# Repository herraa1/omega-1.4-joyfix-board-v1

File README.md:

# Omega Mainboard Revision 1.4 JoyFix Board

This is an interposer board that fixes the existing bug in the joystick circuit of the Omega Mainboard revision 1.4 of the [Omega Home Computer](https://github.com/skiselev/omega) by Sergey Kiselev.

> [!NOTE]
> This fix is not needed if you already have a [Omega Mainboard revision 1.5](https://github.com/skiselev/omega/blob/master/Mainboard.md#changes), which includes the joystick circuit fix.

# The standard MSX joystick circuit

The MSX specification requires that compatible computers provide one or two joystick ports. Nevertheless, most MSX computers have two joystick ports.

The MSX joystick ports are controlled by an AY-3-8910 (or compatible) chip, called the PSG (Programmable Sound Generator). This chip has two general I/O ports IOA and IOB to interface with a micro-processor. In the case of the MSX, IOB is used as OUTPUT and mapped to register #15 of PSG, and IOA is used as INPUT and mapped to register #14 of PSG.

||
|:--|
|MSX Joystick Circuit Diagram|

In the diagram:
- J3 represents joystick port 1
- J4 represents joystick port 2

Each one of the joystick ports has the following pinout:
- 4x INPUT signals
  - pin 1:UP
  - pin 2:DOWN
  - pin 3:LEFT
  - pin 4:RIGHT
- 2x INPUT/OUTPUT signals
  - pin 6:TRIGGER A
  - pin 7:TRIGGER B
- 1x OUTPUT signal
  - pin 8:OUTPUT
- 2x POWER lines
  - pin 5: +5V
  - pin 9: GND

INPUT signals and the input side of INPUT/OUTPUT signals are pulled up by default (making them logical "1" while floating).

The output side of INPUT/OUTPUT signals are buffered with open-collector buffers (74LS07), which leave the outputs floating on logical input "1" and pulled down on logical input "0".

The OUTPUT signal is a push-pull signal, so the output does not float and it is always set to logical "0" or "1".

## IOB I/O port (PSG register #15, OUTPUT) ##

IOB bit 0 controls the output logical level of TRIGGER A (pin 6) of joystick port 1.

IOB bit 1 controls the output logical level of TRIGGER B (pin 7) of joystick port 1.

IOB bit 2 controls the output logical level of TRIGGER A (pin 6) of joystick port 2.

IOB bit 3 controls the output logical level of TRIGGER B (pin 7) of joystick port 2.

IOB bit 4 controls the output logical level of OUTPUT (pin 8) of joystick port 1.

IOB bit 5 controls the output logical level of OUTPUT (pin 8) of joystick port 2.

IOB bit 6 controls which joystick is read ("0" for joystick port 1 and "1" for joystick port 2) as it is connected directly to the Select signal (pin 1) of two 74LS157 quad 2-input multiplexers used to select between the signals of each joystick port.

## IOA I/O port (PSG register #14, INPUT) ##

IOA bits read the status of the direction arrows and triggers of the joysticks. A "1" indicates an inactive arrow/trigger, and a "0" indicates a pressed arrow/trigger.

Before reading an arrow/trigger of a specific joystick, IOB bit 6 must be set accordingly to select the proper joystick port ("0" for port 1, "1" for port 2).

In addition, due to the electrical characteristics of the MSX joystick circuit, reading the trigger buttons input side from IOA require making sure that the output side of IOB is set to "1" before (to avoid pulling down/clobbering the signal).
- In order to read TRIGGER A (bit 4 of IOA) of joystick port 1, one needs to write "1" to bit 0 of IOB.
- In order to read TRIGGER B (bit 5 of IOA) of joystick port 1, one needs to write "1" to bit 1 of IOB.
- In order to read TRIGGER A (bit 4 of IOA) of joystick port 2, one needs to write "1" to bit 2 of IOB.
- In order to read TRIGGER B (bit 5 of IOA) of joystick port 2, one needs to write "1" to bit 3 of IOB.

IOA bit 0 reads the status of the UP arrow.

IOA bit 1 reads the status of the DOWN arrow.

IOA bit 2 reads the status of the LEFT arrow.

IOA bit 3 reads the status of the RIGHT arrow.

IOA bit 4 reads the status of the TRIGGER A button.

IOA bit 5 reads the status of the TRIGGER B button.

# The Problem

As described in the [MRC](https://www.msx.org) hardware forum, @PaxNL discovered an [issue](https://www.msx.org/forum/msx-talk/hardware/msxmakers-support?page=17) with [Super Sokoban](https://www.msxdev.org/2025/01/28/msxdev24-28-super-sokoban/) when trying to play the game with a joystick on the [Omega Home Computer](https://github.com/skiselev/omega).

The game uses the [MSXgl](https://aoineko.org/msxgl/index.php?title=Modules/input) library device detection feature which uses a [MSX-HID](https://www.msx.org/wiki/MSX-HID)-like device fingerprinting to support joysticks and other input devices.

The detection uses OUTPUT (pin 8) of the [joystick port](https://www.msx.org/wiki/General_Purpose_port) to generate a 3-cycle LOW-HIGH-LOW signal. At each of those cycles the low order bits 0-5 of PSG register #14 are read and a fingerprint is calculated based on the results of the 3-cycle reads. The generated fingerprint (hopefully) identifies the connected device type, and from there the proper I/O protocol is used to read/write data to the connected device (which may include using the trigger ports as outputs).

While troubleshooting the issue, @PaxNL and @Arjan determined by looking at the joystick port readouts that there was a problem with the joystick I/O: TRIGGER B on joystick port 1 and TRIGGER A on joystick port 2 were always detected as pressed when the game was run on the Omega Home Computer.

After a deeper analysis with the help of @aoineko, the author of MSXgl, it was determined that there was an implementation bug in the Omega Home Computer joystick circuit diagram which caused exactly that behavior as a result of the software interaction with the buggy hardware.

> [!NOTE]
> The joystick circuit bug does not affect normal operation of joysticks if the software never writes a "0" to the trigger outputs, which is the case for the vast majority of games that use just MSX joysticks and no other devices connected to the joystick ports.
> That's probably why the bug remained undetected for such a long time.

# The Omega mainboard 1.4 joystick circuit

As can be seen on the depicted diagram, the Omega Home Computer PSG circuit tries to mimic the standard MSX joystick circuit, but has a subtle implementation flaw.

Some useful signal mappings to understand the circuit:
- JB0 signal maps to IOB0 signal
- JB1 signal maps to IOB1 signal
- JB2 signal maps to IOB2 signal
- JB3 signal maps to IOB3 signal

If we look closely at the connection of the trigger output signals to the open-collector buffer inputs and the connection of the open-collector buffer outputs to the joystick port signals we can see that:
- :white_check_mark: the output of the open-collector buffer corresponding to signal JB0 (IOB0) is connected to joystick port 1 trigger A (TRG1_A)
- :x: the output of the open-collector buffer corresponding to signal JB1 (IOB1) is incorrectly connected to joystick port 2 trigger A (TRG1_B)
- :x: the output of the open-collector buffer corresponding to signal JB2 (IOB2) is incorrectly connected to joystick port 1 trigger B (TRG2_A)
- :white_check_mark: the output of the open-collector buffer corresponding to signal JB3 (IOB3) is connected to joystick port 2 trigger B (TRG2_B)

Exactly the two signals that were incorrectly read (joystick port 2 trigger A and joystick port 1 trigger B) are the signals that are incorrectly wired.

The incorrect wiring is probably caused by the confusing naming convention used for the trigger signal labels which is prone to errors (TRGx_y means trigger x of joystick y, with y=A|B and x=1|2).

# The fix

The circuit can be easily fixed by re-routing the affected signals to make them available at the right place.

In the Omega Mainboard 1.4 joystick circuit we have the following connections related to the triggers, taking into account the functional pinout of the [74LS07](https://www.ti.com/lit/ds/symlink/sn74ls07.pdf):
- input `Pin 11` of U42 (connected to JB2/IOB2) outputs to `Pin 10` of U42 (incorrectly connected to joystick port 1 trigger B, aka TRG2_A)
- input `Pin 13` of U42 (connected to JB1/IOB1) outputs to `Pin 12` of U42 (incorrectly connected to joystick port 2 trigger A, aka TRG1_B)

A clean and easy approach to fix the circuit is to use an interposer board at U42 (74LS07 open-collector buffer) that performs the needed re-mapping of signals.

The idea of the interposer board was brought up by Ludo and shared on [issue #56](https://github.com/skiselev/omega/issues/56) of the [Omega github page](https://github.com/skiselev/omega) where you can see a photo of his CNC fabricated interposer board.

So to re-route the signals to match the MSX standard joystick circuit we can map the U42-original signals to a new set of U42-interposed signals (where the 74LS07 will be actually connected), like this:
- Connect `Pin 10 of U42-interposed` (buffered output of Pin 11 of U42-interposed which connects to JB2/IOB2) to `Pin 12 of U42-original` (connected to joystick port 2 trigger A, aka TRG1_B), so that Pin 11 of U42-original (JB2/IOB2) outputs to Pin 12 of U42-original (joystick port 2 trigger A) ( `yellow` path on the diagram)
- Connect `Pin 12 of U42-interposed` (buffered output of Pin 13 of U42-interposed which connects to JB1/IOB1) to `Pin 10 of U42-original` (connected to joystick port 1 trigger B, aka TRG2_A), so that Pin 13 of U42-original (JB1/IOB1) outputs to Pin 10 of U42-original (joystick port 1 trigger B) ( `green` path on the diagram)
- Connect all other Pins of U42-interposed to the same Pins of U42-original (i.e Pin 1 to Pin 1, Pin 2 to Pin 2, etc.) ( solid `pink` paths on the diagram)

Summarizing, after the re-routing we have fixed the issue:
- `Pin 11 of U42-original` (connected to JB2/IOB2) outputs to `Pin 12 of U42-original` (connected to joystick port 2 trigger A)
- `Pin 13 of U42-original` (connected to JB1/IOB1) outputs to `Pin 10 of U42-original` (connected to joystick port 1 trigger B)

And the complete trigger connection diagram matches now the original MSX joystick circuit diagram:
- :white_check_mark: the output at the open-collector buffer corresponding to signal JB0 (IOB0) is connected to joystick port 1 trigger A (TRG1_A)
- :white_check_mark: the output at the open-collector buffer corresponding to signal JB1 (IOB1) is connected to joystick port 1 trigger B (TRG2_A)
- :white_check_mark: the output at the open-collector buffer corresponding to signal JB2 (IOB2) is connected to joystick port 2 trigger A (TRG1_B)
- :white_check_mark: the output at the open-collector buffer corresponding to signal JB3 (IOB3) is connected to joystick port 2 trigger B (TRG2_B)

# Hardware

## [Omega-1.4-U42-joyfix-v1-Build1](hardware/kicad/omega-1.4-joyfix-board-v1-Build1/)

:white_check_mark: This board has been successfully built and tested.

[Bill Of Materials (BoM)](https://htmlpreview.github.io/?https://raw.githubusercontent.com/herraa1/omega-1.4-joyfix-board-v1/main/hardware/kicad/omega-1.4-joyfix-board-v1-Build1/bom/ibom.html)

[Schematic and PCB](https://kicanvas.org/?github=https%3A%2F%2Fgithub.com%2Fherraa1%2Fomega-1.4-joyfix-board-v1%2Ftree%2Fmain%2Fhardware%2Fkicad%2Fomega-1.4-joyfix-board-v1-Build1)

## PCB Manufacturing tips

As the joyfix board is super small, some PCB manufacturers may make extra charges when building standalone prototypes or panelizing the boards using v-cuts.

One way to avoid the extra costs is panelizing the joyfix board using "mouse bites".

# Build instructions

## Required materials

* 2x 2.54mm pitch male-male header L10 7P
* 1x DIP14 circular IC socket

## Step by step instructions

1. Determine the large pad side of the 7P headers.

2. Temporarily insert the two 7P headers into the DIP14 circular IC socket to perfectly align the headers before soldering them to the joyfix board PCB.

You need to insert the headers so that the large pad side stays on the top, and the small pads side is inserted into the socket.

3. Insert the PCB into the two 7P headers using the small circular pads, making sure the PCB top mark remains at the top.

4. Solder the headers to the PCB from the top side and then remove the DIP14 IC socket (it was used temporarily just for alignment purposes).

5. Trim the headers on the top side to avoid interfering with the DIP14 IC socket when installed permanently.

6. Insert the DIP14 IC socket into the large pads of the PCB from the top side in preparation for soldering.

7. Solder the DIP14 IC socket to the joyfix board PCB from the bottom side, making sure you don't accidentally touch the header plastics while soldering.

8. Clean the board with 99.9% Isopropyl Alcohol (IPA) and proceed to installation.

# Installation instructions

## Step by step instructions

1. Locate the U42 74LS07 IC chip on the Omega Home Computer.

It is a DIP14 IC available near the joystick port 2.

2. Remove the 74LS07 chip from the U42 socket, insert it into the joyfix board socket, and then insert the joyfix board into the U42 socket.

Respect the IC notch markings when orienting both the 74LS07 and the joyfix board for insertion.

Make sure you properly align the joyfix board header pins to the U42 socket to make a good insertion without damaging the U42 socket.

# Validating the fix

The [MSXJIO](https://github.com/louthrax/MSXJIO) project by @Louthrax is a fun way to test that the Omega mainboard 1.4 joystick hardware bug is gone when using the joyfix board.

You will need:
- A MSX JIO client in ROM format like JMSXDOS1.rom available in [JIO_Client_MSXDOS1_1_0.zip ](https://github.com/louthrax/MSXJIO/releases)
- A DSK image of your choice
- A MSX JIO compatible hardware as described in the [hardware section](https://github.com/louthrax/MSXJIO?tab=readme-ov-file#hardware) of the MSXJIO project.
- A [MSX JIO server](https://github.com/louthrax/MSXJIO?tab=readme-ov-file#server-details) for your operating system of choice

See the MSXJIO project for additional [details and instructions](https://github.com/louthrax/MSXJIO?tab=readme-ov-file#msxjio).

The idea is to flash the MSX JIO client ROM to a ROM cartridge (for example, the [RISKYMSX](https://github.com/arkadiuszmakarenko/RISKYMSX)), connect the MSX JIO hardware between your PC and MSX, start the MSX JIO server on your PC with your DSK of choice selected, and boot your MSX with the MSX JIO client ROM. The MSX will boot and use the DSK in your PC as a mass storage device. Coolio!

## Omega 1.4 without the joyfix board

## Omega 1.4 with the joyfix board

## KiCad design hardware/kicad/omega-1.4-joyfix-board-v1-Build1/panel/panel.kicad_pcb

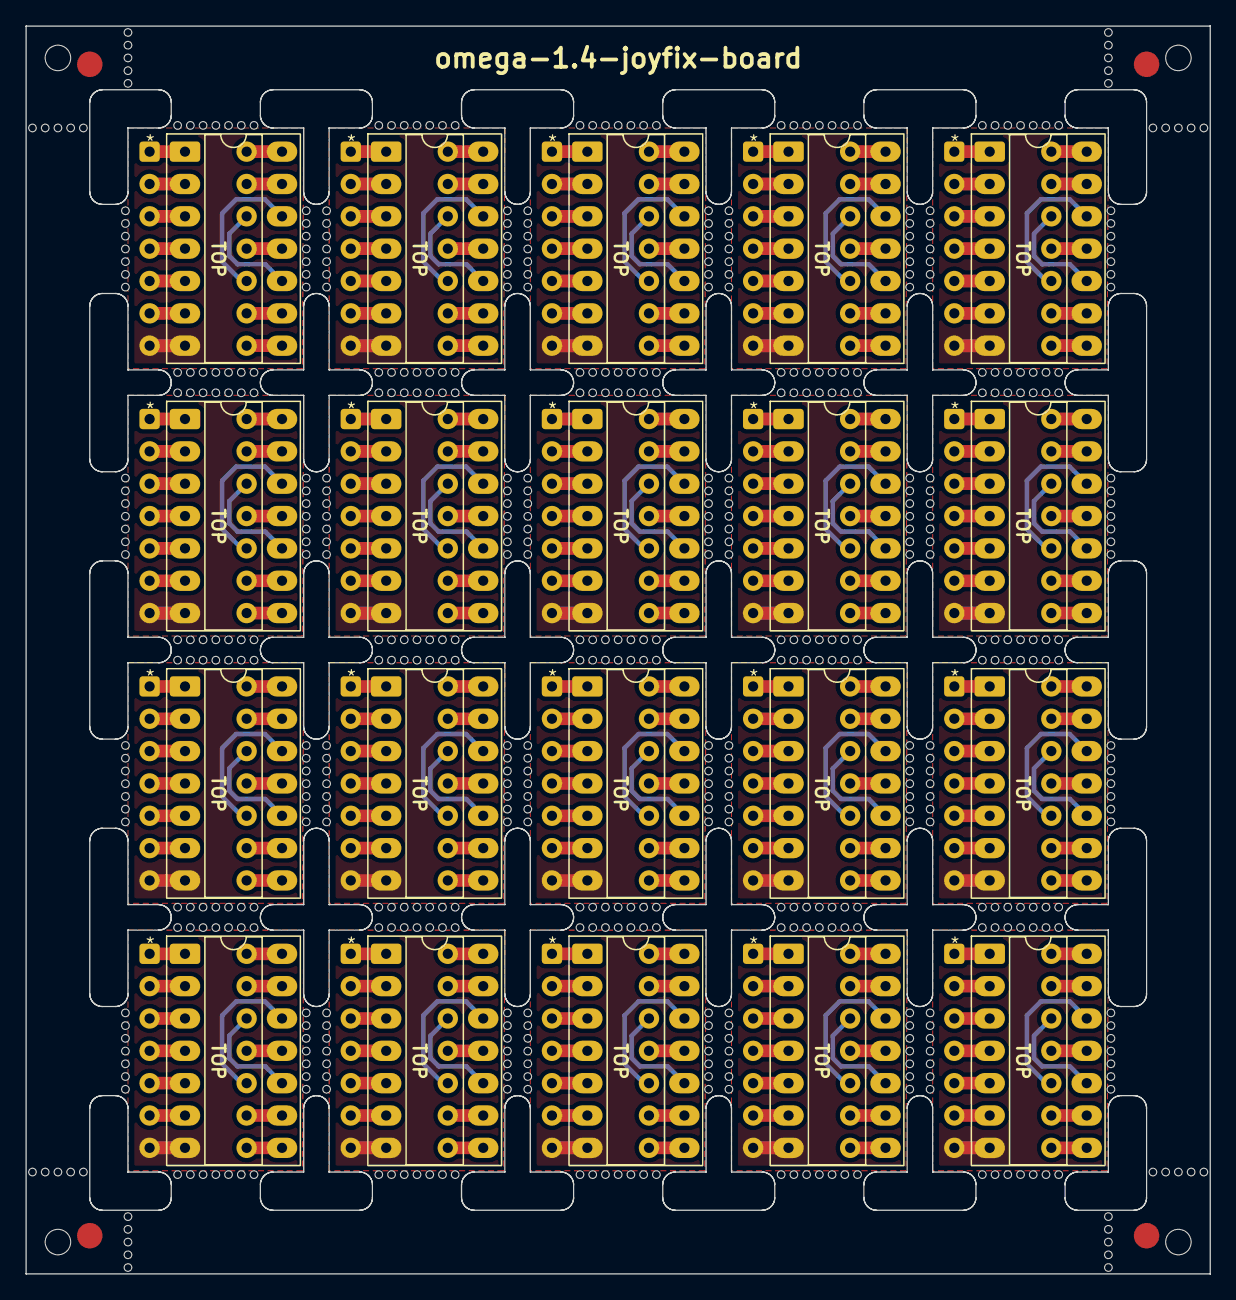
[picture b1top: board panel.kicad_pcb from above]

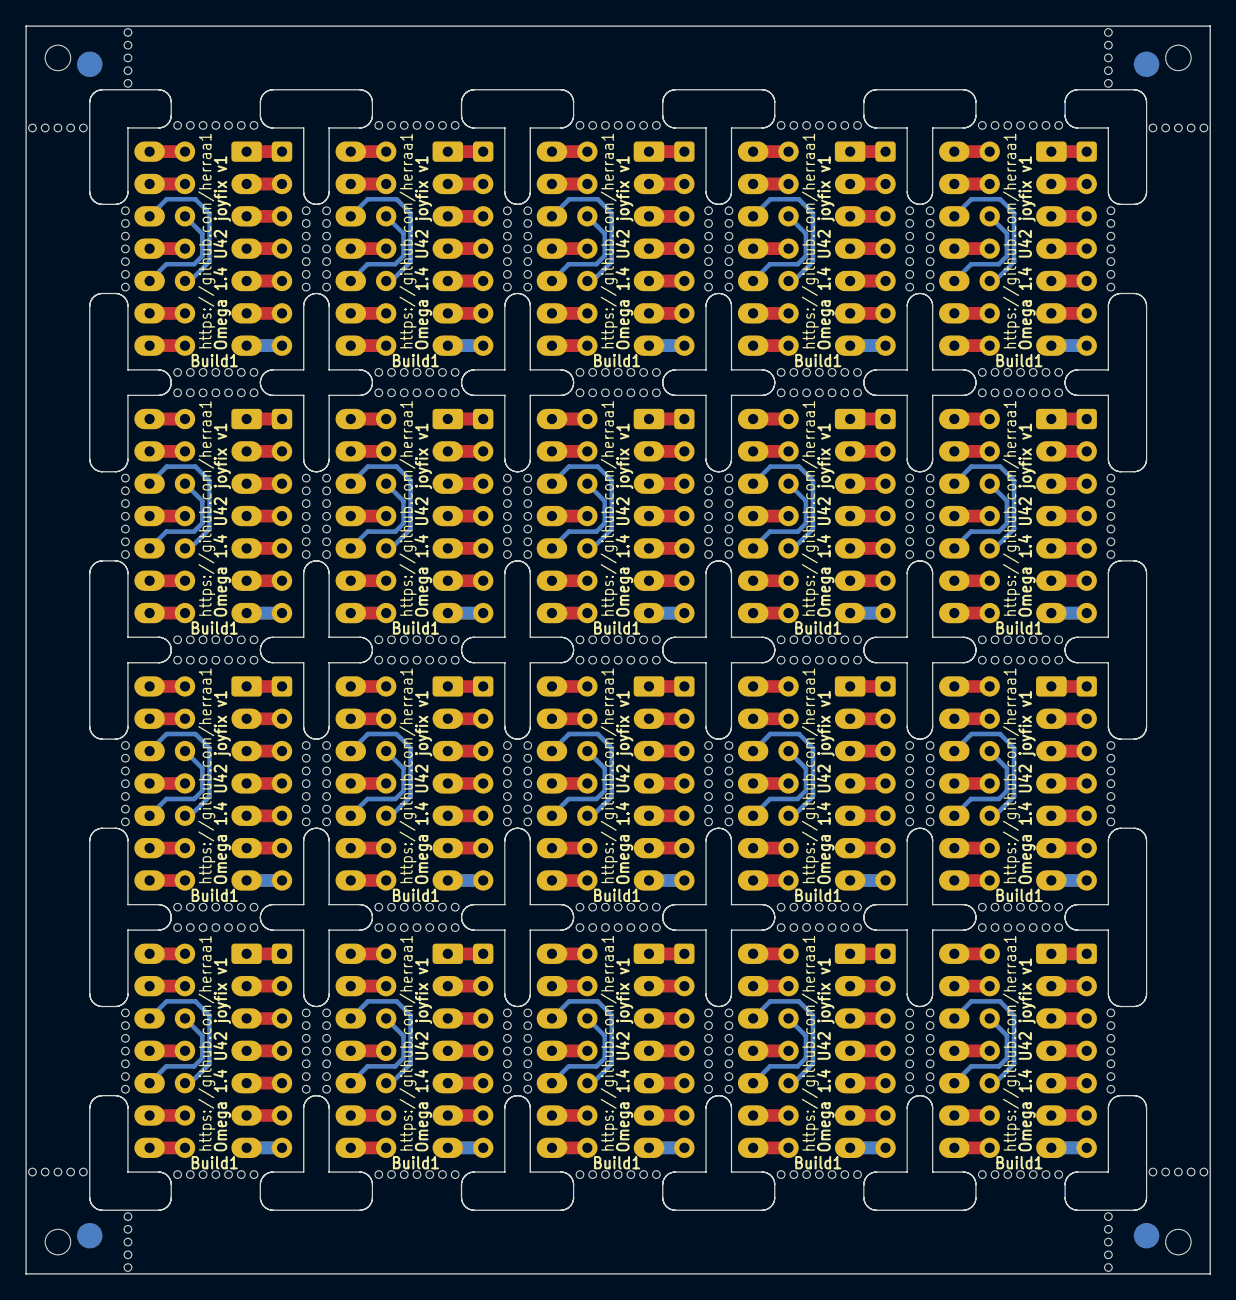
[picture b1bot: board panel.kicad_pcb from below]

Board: 2 copper layers, 93.0 x 98.0 mm, 652 parts (4 on the bottom side), 280 nets.

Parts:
J1, J1#2, J1#3, J1#4, J1#5, J1#6, J1#7, J1#8, J1#9, J1#10, J1#11, J1#12, J1#13, J1#14, J1#15, J1#16, J1#17, J1#18, J1#19, J1#20: To Motherboard; DIP-14_W7.62mm_Socket_Custom
J2, J2#2, J2#3, J2#4, J2#5, J2#6, J2#7, J2#8, J2#9, J2#10, J2#11, J2#12, J2#13, J2#14, J2#15, J2#16, J2#17, J2#18, J2#19, J2#20: To 74LS07; DIP-14_W7.62mm_Socket_LongPads
KiKit_FID_B_1, KiKit_FID_B_2, KiKit_FID_B_3, KiKit_FID_B_4: Fiducial
KiKit_FID_T_1, KiKit_FID_T_2, KiKit_FID_T_3, KiKit_FID_T_4: Fiducial
KiKit_MB_1_2, KiKit_MB_1_3, KiKit_MB_1_4, KiKit_MB_1_5, KiKit_MB_1_6, KiKit_MB_1_7, KiKit_MB_1_8, KiKit_MB_2_2, KiKit_MB_2_3, KiKit_MB_2_4, KiKit_MB_2_5, KiKit_MB_2_6, KiKit_MB_2_7, KiKit_MB_2_8, KiKit_MB_3_2, KiKit_MB_3_3, KiKit_MB_3_4, KiKit_MB_3_5, KiKit_MB_3_6, KiKit_MB_3_7, KiKit_MB_3_8, KiKit_MB_4_2, KiKit_MB_4_3, KiKit_MB_4_4, KiKit_MB_4_5, KiKit_MB_4_6, KiKit_MB_4_7, KiKit_MB_4_8, KiKit_MB_5_2, KiKit_MB_5_3, KiKit_MB_5_4, KiKit_MB_5_5, KiKit_MB_5_6, KiKit_MB_5_7, KiKit_MB_5_8, KiKit_MB_6_2, KiKit_MB_6_3, KiKit_MB_6_4, KiKit_MB_6_5, KiKit_MB_6_6, KiKit_MB_6_7, KiKit_MB_6_8, KiKit_MB_7_2, KiKit_MB_7_3, KiKit_MB_7_4, KiKit_MB_7_5, KiKit_MB_7_6, KiKit_MB_7_7, KiKit_MB_7_8, KiKit_MB_8_2, KiKit_MB_8_3, KiKit_MB_8_4, KiKit_MB_8_5, KiKit_MB_8_6, KiKit_MB_8_7, KiKit_MB_8_8, KiKit_MB_9_2, KiKit_MB_9_3, KiKit_MB_9_4, KiKit_MB_9_5, KiKit_MB_9_6, KiKit_MB_9_7, KiKit_MB_9_8, KiKit_MB_10_2, KiKit_MB_10_3, KiKit_MB_10_4, KiKit_MB_10_5, KiKit_MB_10_6, KiKit_MB_10_7, KiKit_MB_10_8, KiKit_MB_11_2, KiKit_MB_11_3, KiKit_MB_11_4, KiKit_MB_11_5, KiKit_MB_11_6, KiKit_MB_11_7, KiKit_MB_11_8, KiKit_MB_12_2, KiKit_MB_12_3, KiKit_MB_12_4, KiKit_MB_12_5, KiKit_MB_12_6, KiKit_MB_12_7, KiKit_MB_12_8, KiKit_MB_13_2, KiKit_MB_13_3, KiKit_MB_13_4, KiKit_MB_13_5, KiKit_MB_13_6, KiKit_MB_13_7, KiKit_MB_13_8, KiKit_MB_14_2, KiKit_MB_14_3, KiKit_MB_14_4, KiKit_MB_14_5, KiKit_MB_14_6, KiKit_MB_14_7, KiKit_MB_14_8, KiKit_MB_15_2, KiKit_MB_15_3, KiKit_MB_15_4, KiKit_MB_15_5, KiKit_MB_15_6, KiKit_MB_15_7, KiKit_MB_15_8, KiKit_MB_16_2, KiKit_MB_16_3, KiKit_MB_16_4, KiKit_MB_16_5, KiKit_MB_16_6, KiKit_MB_16_7, KiKit_MB_16_8, KiKit_MB_17_2, KiKit_MB_17_3, KiKit_MB_17_4, KiKit_MB_17_5, KiKit_MB_17_6, KiKit_MB_17_7, KiKit_MB_17_8, KiKit_MB_18_2, KiKit_MB_18_3, KiKit_MB_18_4, KiKit_MB_18_5, KiKit_MB_18_6, KiKit_MB_18_7, KiKit_MB_18_8, KiKit_MB_19_2, KiKit_MB_19_3, KiKit_MB_19_4, KiKit_MB_19_5, KiKit_MB_19_6, KiKit_MB_19_7, KiKit_MB_19_8, KiKit_MB_20_2, KiKit_MB_20_3, KiKit_MB_20_4, KiKit_MB_20_5, KiKit_MB_20_6, KiKit_MB_20_7, KiKit_MB_20_8, KiKit_MB_21_2, KiKit_MB_21_3, KiKit_MB_21_4, KiKit_MB_21_5, KiKit_MB_21_6, KiKit_MB_21_7, KiKit_MB_21_8, KiKit_MB_22_2, KiKit_MB_22_3, KiKit_MB_22_4, KiKit_MB_22_5, KiKit_MB_22_6, KiKit_MB_22_7, KiKit_MB_22_8, KiKit_MB_23_2, KiKit_MB_23_3, KiKit_MB_23_4, KiKit_MB_23_5, KiKit_MB_23_6, KiKit_MB_23_7, KiKit_MB_23_8, KiKit_MB_24_2, KiKit_MB_24_3, KiKit_MB_24_4, KiKit_MB_24_5, KiKit_MB_24_6, KiKit_MB_24_7, KiKit_MB_24_8, KiKit_MB_25_2, KiKit_MB_25_3, KiKit_MB_25_4, KiKit_MB_25_5, KiKit_MB_25_6, KiKit_MB_25_7, KiKit_MB_25_8, KiKit_MB_26_2, KiKit_MB_26_3, KiKit_MB_26_4, KiKit_MB_26_5, KiKit_MB_26_6, KiKit_MB_26_7, KiKit_MB_26_8, KiKit_MB_27_2, KiKit_MB_27_3, KiKit_MB_27_4, KiKit_MB_27_5, KiKit_MB_27_6, KiKit_MB_27_7, KiKit_MB_27_8, KiKit_MB_28_2, KiKit_MB_28_3, KiKit_MB_28_4, KiKit_MB_28_5, KiKit_MB_28_6, KiKit_MB_28_7, KiKit_MB_28_8, KiKit_MB_29_2, KiKit_MB_29_3, KiKit_MB_29_4, KiKit_MB_29_5, KiKit_MB_29_6, KiKit_MB_29_7, KiKit_MB_29_8, KiKit_MB_30_2, KiKit_MB_30_3, KiKit_MB_30_4, KiKit_MB_30_5, KiKit_MB_30_6, KiKit_MB_30_7, KiKit_MB_30_8, KiKit_MB_31_2, KiKit_MB_31_3, KiKit_MB_31_4, KiKit_MB_31_5, KiKit_MB_31_6, KiKit_MB_31_7, KiKit_MB_31_8, KiKit_MB_32_2, KiKit_MB_32_3, KiKit_MB_32_4, KiKit_MB_32_5, KiKit_MB_32_6, KiKit_MB_32_7, KiKit_MB_32_8, KiKit_MB_33_2, KiKit_MB_33_3, KiKit_MB_33_4, KiKit_MB_33_5, KiKit_MB_33_6, KiKit_MB_33_7, KiKit_MB_33_8, KiKit_MB_34_2, KiKit_MB_34_3, KiKit_MB_34_4, KiKit_MB_34_5, KiKit_MB_34_6, KiKit_MB_34_7, KiKit_MB_34_8, KiKit_MB_35_2, KiKit_MB_35_3, KiKit_MB_35_4, KiKit_MB_35_5, KiKit_MB_35_6, KiKit_MB_35_7, KiKit_MB_35_8, KiKit_MB_36_2, KiKit_MB_36_3, KiKit_MB_36_4, KiKit_MB_36_5, KiKit_MB_36_6, KiKit_MB_36_7, KiKit_MB_36_8, KiKit_MB_37_2, KiKit_MB_37_3, KiKit_MB_37_4, KiKit_MB_37_5, KiKit_MB_37_6, KiKit_MB_37_7, KiKit_MB_37_8, KiKit_MB_38_2, KiKit_MB_38_3, KiKit_MB_38_4, KiKit_MB_38_5, KiKit_MB_38_6, KiKit_MB_38_7, KiKit_MB_38_8, KiKit_MB_39_2, KiKit_MB_39_3, KiKit_MB_39_4, KiKit_MB_39_5, KiKit_MB_39_6, KiKit_MB_39_7, KiKit_MB_39_8, KiKit_MB_40_2, KiKit_MB_40_3, KiKit_MB_40_4, KiKit_MB_40_5, KiKit_MB_40_6, KiKit_MB_40_7, KiKit_MB_40_8, KiKit_MB_41_2, KiKit_MB_41_3, KiKit_MB_41_4, KiKit_MB_41_5, KiKit_MB_41_6, KiKit_MB_41_7, KiKit_MB_41_8, KiKit_MB_42_2, KiKit_MB_42_3, KiKit_MB_42_4, KiKit_MB_42_5, KiKit_MB_42_6, KiKit_MB_42_7, KiKit_MB_42_8, KiKit_MB_43_2, KiKit_MB_43_3, KiKit_MB_43_4, KiKit_MB_43_5, KiKit_MB_43_6, KiKit_MB_43_7, KiKit_MB_43_8, KiKit_MB_44_2, KiKit_MB_44_3, KiKit_MB_44_4, KiKit_MB_44_5, KiKit_MB_44_6, KiKit_MB_44_7, KiKit_MB_44_8, KiKit_MB_45_2, KiKit_MB_45_3, KiKit_MB_45_4, KiKit_MB_45_5, KiKit_MB_45_6, KiKit_MB_45_7, KiKit_MB_45_8, KiKit_MB_46_2, KiKit_MB_46_3, KiKit_MB_46_4, KiKit_MB_46_5, KiKit_MB_46_6, KiKit_MB_46_7, KiKit_MB_46_8, KiKit_MB_47_2, KiKit_MB_47_3, KiKit_MB_47_4, KiKit_MB_47_5, KiKit_MB_47_6, KiKit_MB_47_7, KiKit_MB_47_8, KiKit_MB_48_2, KiKit_MB_48_3, KiKit_MB_48_4, KiKit_MB_48_5, KiKit_MB_48_6, KiKit_MB_48_7, KiKit_MB_48_8, KiKit_MB_49_2, KiKit_MB_49_3, KiKit_MB_49_4, KiKit_MB_49_5, KiKit_MB_49_6, KiKit_MB_49_7, KiKit_MB_49_8, KiKit_MB_50_2, KiKit_MB_50_3, KiKit_MB_50_4, KiKit_MB_50_5, KiKit_MB_50_6, KiKit_MB_50_7, KiKit_MB_50_8, KiKit_MB_51_2, KiKit_MB_51_3, KiKit_MB_51_4, KiKit_MB_51_5, KiKit_MB_51_6, KiKit_MB_51_7, KiKit_MB_51_8, KiKit_MB_52_2, KiKit_MB_52_3, KiKit_MB_52_4, KiKit_MB_52_5, KiKit_MB_52_6, KiKit_MB_52_7, KiKit_MB_52_8, KiKit_MB_53_2, KiKit_MB_53_3, KiKit_MB_53_4, KiKit_MB_53_5, KiKit_MB_53_6, KiKit_MB_53_7, KiKit_MB_53_8, KiKit_MB_54_2, KiKit_MB_54_3, KiKit_MB_54_4, KiKit_MB_54_5, KiKit_MB_54_6, KiKit_MB_54_7, KiKit_MB_54_8, KiKit_MB_55_2, KiKit_MB_55_3, KiKit_MB_55_4, KiKit_MB_55_5, KiKit_MB_55_6, KiKit_MB_55_7, KiKit_MB_55_8, KiKit_MB_56_2, KiKit_MB_56_3, KiKit_MB_56_4, KiKit_MB_56_5, KiKit_MB_56_6, KiKit_MB_56_7, KiKit_MB_56_8, KiKit_MB_57_2, KiKit_MB_57_3, KiKit_MB_57_4, KiKit_MB_57_5, KiKit_MB_57_6, KiKit_MB_57_7, KiKit_MB_57_8, KiKit_MB_58_2, KiKit_MB_58_3, KiKit_MB_58_4, KiKit_MB_58_5, KiKit_MB_58_6, KiKit_MB_58_7, KiKit_MB_58_8, KiKit_MB_59_2, KiKit_MB_59_3, KiKit_MB_59_4, KiKit_MB_59_5, KiKit_MB_59_6, KiKit_MB_59_7, KiKit_MB_59_8, KiKit_MB_60_2, KiKit_MB_60_3, KiKit_MB_60_4, KiKit_MB_60_5, KiKit_MB_60_6, KiKit_MB_60_7, KiKit_MB_60_8, KiKit_MB_61_2, KiKit_MB_61_3, KiKit_MB_61_4, KiKit_MB_61_5, KiKit_MB_61_6, KiKit_MB_61_7, KiKit_MB_61_8, KiKit_MB_62_2, KiKit_MB_62_3, KiKit_MB_62_4, KiKit_MB_62_5, KiKit_MB_62_6, KiKit_MB_62_7, KiKit_MB_62_8, KiKit_MB_63_2, KiKit_MB_63_3, KiKit_MB_63_4, KiKit_MB_63_5, KiKit_MB_63_6, KiKit_MB_63_7, KiKit_MB_63_8, KiKit_MB_64_2, KiKit_MB_64_3, KiKit_MB_64_4, KiKit_MB_64_5, KiKit_MB_64_6, KiKit_MB_64_7, KiKit_MB_64_8, KiKit_MB_65_2, KiKit_MB_65_3, KiKit_MB_65_4, KiKit_MB_65_5, KiKit_MB_65_6, KiKit_MB_65_7, KiKit_MB_65_8, KiKit_MB_66_2, KiKit_MB_66_3, KiKit_MB_66_4, KiKit_MB_66_5, KiKit_MB_66_6, KiKit_MB_66_7, KiKit_MB_66_8, KiKit_MB_67_2, KiKit_MB_67_3, KiKit_MB_67_4, KiKit_MB_67_5, KiKit_MB_67_6, KiKit_MB_67_7, KiKit_MB_67_8, KiKit_MB_68_2, KiKit_MB_68_3, KiKit_MB_68_4, KiKit_MB_68_5, KiKit_MB_68_6, KiKit_MB_68_7, KiKit_MB_68_8, KiKit_MB_69_2, KiKit_MB_69_3, KiKit_MB_69_4, KiKit_MB_69_5, KiKit_MB_69_6, KiKit_MB_69_7, KiKit_MB_69_8, KiKit_MB_70_2, KiKit_MB_70_3, KiKit_MB_70_4, KiKit_MB_70_5, KiKit_MB_70_6, KiKit_MB_70_7, KiKit_MB_70_8, KiKit_MB_71_2, KiKit_MB_71_3, KiKit_MB_71_4, KiKit_MB_71_5, KiKit_MB_71_6, KiKit_MB_71_7, KiKit_MB_71_8, KiKit_MB_72_2, KiKit_MB_72_3, KiKit_MB_72_4, KiKit_MB_72_5, KiKit_MB_72_6, KiKit_MB_72_7, KiKit_MB_72_8, KiKit_MB_73_2, KiKit_MB_73_3, KiKit_MB_73_4, KiKit_MB_73_5, KiKit_MB_73_6, KiKit_MB_73_7, KiKit_MB_73_8, KiKit_MB_74_2, KiKit_MB_74_3, KiKit_MB_74_4, KiKit_MB_74_5, KiKit_MB_74_6, KiKit_MB_74_7, KiKit_MB_74_8, KiKit_MB_75_2, KiKit_MB_75_3, KiKit_MB_75_4, KiKit_MB_75_5, KiKit_MB_75_6, KiKit_MB_75_7, KiKit_MB_75_8, KiKit_MB_76_2, KiKit_MB_76_3, KiKit_MB_76_4, KiKit_MB_76_5, KiKit_MB_76_6, KiKit_MB_76_7, KiKit_MB_76_8, KiKit_MB_77_2, KiKit_MB_77_3, KiKit_MB_77_4, KiKit_MB_77_5, KiKit_MB_77_6, KiKit_MB_77_7, KiKit_MB_77_8, KiKit_MB_78_2, KiKit_MB_78_3, KiKit_MB_78_4, KiKit_MB_78_5, KiKit_MB_78_6, KiKit_MB_78_7, KiKit_MB_78_8, KiKit_MB_79_2, KiKit_MB_79_3, KiKit_MB_79_4, KiKit_MB_79_5, KiKit_MB_79_6, KiKit_MB_79_7, KiKit_MB_79_8, KiKit_MB_80_2, KiKit_MB_80_3, KiKit_MB_80_4, KiKit_MB_80_5, KiKit_MB_80_6, KiKit_MB_80_7, KiKit_MB_80_8, KiKit_MB_81_2, KiKit_MB_81_3, KiKit_MB_81_4, KiKit_MB_81_5, KiKit_MB_81_6, KiKit_MB_82_2, KiKit_MB_82_3, KiKit_MB_82_4, KiKit_MB_82_5, KiKit_MB_82_6, KiKit_MB_83_2, KiKit_MB_83_3, KiKit_MB_83_4, KiKit_MB_83_5, KiKit_MB_83_6, KiKit_MB_84_2, KiKit_MB_84_3, KiKit_MB_84_4, KiKit_MB_84_5, KiKit_MB_84_6, KiKit_MB_85_2, KiKit_MB_85_3, KiKit_MB_85_4, KiKit_MB_85_5, KiKit_MB_85_6, KiKit_MB_86_2, KiKit_MB_86_3, KiKit_MB_86_4, KiKit_MB_86_5, KiKit_MB_86_6, KiKit_MB_87_2, KiKit_MB_87_3, KiKit_MB_87_4, KiKit_MB_87_5, KiKit_MB_87_6, KiKit_MB_88_2, KiKit_MB_88_3, KiKit_MB_88_4, KiKit_MB_88_5, KiKit_MB_88_6: NPTH
KiKit_TO_1, KiKit_TO_2, KiKit_TO_3, KiKit_TO_4: NPTH

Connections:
Board_0-/GND: J1#19.7, J2#7.7
Board_0-/J1TRG1: J1#19.2, J2#7.2
Board_0-/J1TRG2: J1#19.10, J2#7.12
Board_0-/J2TRG1: J1#19.12, J2#7.10
Board_0-/J2TRG2: J1#19.4, J2#7.4
Board_0-/JB0: J1#19.1, J2#7.1
Board_0-/JB1: J1#19.13, J2#7.13
Board_0-/JB2: J1#19.11, J2#7.11
Board_0-/JB3: J1#19.3, J2#7.3
Board_0-/VCC: J1#19.14, J2#7.14
Board_0-Net-(J1-Pin_5): J1#19.5, J2#7.5
Board_0-Net-(J1-Pin_6): J1#19.6, J2#7.6
Board_0-Net-(J1-Pin_8): J1#19.8, J2#7.8
Board_0-Net-(J1-Pin_9): J1#19.9, J2#7.9
Board_1-/GND: J1#8.7, J2#13.7
Board_1-/J1TRG1: J1#8.2, J2#13.2
Board_1-/J1TRG2: J1#8.10, J2#13.12
Board_1-/J2TRG1: J1#8.12, J2#13.10
Board_1-/J2TRG2: J1#8.4, J2#13.4
Board_1-/JB0: J1#8.1, J2#13.1
Board_1-/JB1: J1#8.13, J2#13.13
Board_1-/JB2: J1#8.11, J2#13.11
Board_1-/JB3: J1#8.3, J2#13.3
Board_1-/VCC: J1#8.14, J2#13.14
Board_1-Net-(J1-Pin_5): J1#8.5, J2#13.5
Board_1-Net-(J1-Pin_6): J1#8.6, J2#13.6
Board_1-Net-(J1-Pin_8): J1#8.8, J2#13.8
Board_1-Net-(J1-Pin_9): J1#8.9, J2#13.9
Board_2-/GND: J1#14.7, J2#6.7
Board_2-/J1TRG1: J1#14.2, J2#6.2
Board_2-/J1TRG2: J1#14.10, J2#6.12
Board_2-/J2TRG1: J1#14.12, J2#6.10
Board_2-/J2TRG2: J1#14.4, J2#6.4
Board_2-/JB0: J1#14.1, J2#6.1
Board_2-/JB1: J1#14.13, J2#6.13
Board_2-/JB2: J1#14.11, J2#6.11
Board_2-/JB3: J1#14.3, J2#6.3
Board_2-/VCC: J1#14.14, J2#6.14
Board_2-Net-(J1-Pin_5): J1#14.5, J2#6.5
Board_2-Net-(J1-Pin_6): J1#14.6, J2#6.6
Board_2-Net-(J1-Pin_8): J1#14.8, J2#6.8
Board_2-Net-(J1-Pin_9): J1#14.9, J2#6.9
Board_3-/GND: J1#9.7, J2#17.7
Board_3-/J1TRG1: J1#9.2, J2#17.2
Board_3-/J1TRG2: J1#9.10, J2#17.12
Board_3-/J2TRG1: J1#9.12, J2#17.10
Board_3-/J2TRG2: J1#9.4, J2#17.4
Board_3-/JB0: J1#9.1, J2#17.1
Board_3-/JB1: J1#9.13, J2#17.13
Board_3-/JB2: J1#9.11, J2#17.11
Board_3-/JB3: J1#9.3, J2#17.3
Board_3-/VCC: J1#9.14, J2#17.14
Board_3-Net-(J1-Pin_5): J1#9.5, J2#17.5
Board_3-Net-(J1-Pin_6): J1#9.6, J2#17.6
Board_3-Net-(J1-Pin_8): J1#9.8, J2#17.8
Board_3-Net-(J1-Pin_9): J1#9.9, J2#17.9
Board_4-/GND: J1.7, J2#2.7
Board_4-/J1TRG1: J1.2, J2#2.2
Board_4-/J1TRG2: J1.10, J2#2.12
Board_4-/J2TRG1: J1.12, J2#2.10
Board_4-/J2TRG2: J1.4, J2#2.4
Board_4-/JB0: J1.1, J2#2.1
Board_4-/JB1: J1.13, J2#2.13
Board_4-/JB2: J1.11, J2#2.11
Board_4-/JB3: J1.3, J2#2.3
Board_4-/VCC: J1.14, J2#2.14
Board_4-Net-(J1-Pin_5): J1.5, J2#2.5
Board_4-Net-(J1-Pin_6): J1.6, J2#2.6
Board_4-Net-(J1-Pin_8): J1.8, J2#2.8
Board_4-Net-(J1-Pin_9): J1.9, J2#2.9
Board_5-/GND: J1#6.7, J2#18.7
Board_5-/J1TRG1: J1#6.2, J2#18.2
Board_5-/J1TRG2: J1#6.10, J2#18.12
Board_5-/J2TRG1: J1#6.12, J2#18.10
Board_5-/J2TRG2: J1#6.4, J2#18.4
Board_5-/JB0: J1#6.1, J2#18.1
Board_5-/JB1: J1#6.13, J2#18.13
Board_5-/JB2: J1#6.11, J2#18.11
Board_5-/JB3: J1#6.3, J2#18.3
Board_5-/VCC: J1#6.14, J2#18.14
Board_5-Net-(J1-Pin_5): J1#6.5, J2#18.5
Board_5-Net-(J1-Pin_6): J1#6.6, J2#18.6
Board_5-Net-(J1-Pin_8): J1#6.8, J2#18.8
Board_5-Net-(J1-Pin_9): J1#6.9, J2#18.9
Board_6-/GND: J1#15.7, J2#10.7
Board_6-/J1TRG1: J1#15.2, J2#10.2
Board_6-/J1TRG2: J1#15.10, J2#10.12
Board_6-/J2TRG1: J1#15.12, J2#10.10
Board_6-/J2TRG2: J1#15.4, J2#10.4
Board_6-/JB0: J1#15.1, J2#10.1
Board_6-/JB1: J1#15.13, J2#10.13
Board_6-/JB2: J1#15.11, J2#10.11
Board_6-/JB3: J1#15.3, J2#10.3
Board_6-/VCC: J1#15.14, J2#10.14
Board_6-Net-(J1-Pin_5): J1#15.5, J2#10.5
Board_6-Net-(J1-Pin_6): J1#15.6, J2#10.6
Board_6-Net-(J1-Pin_8): J1#15.8, J2#10.8
Board_6-Net-(J1-Pin_9): J1#15.9, J2#10.9
Board_7-/GND: J1#4.7, J2#12.7
Board_7-/J1TRG1: J1#4.2, J2#12.2
Board_7-/J1TRG2: J1#4.10, J2#12.12
Board_7-/J2TRG1: J1#4.12, J2#12.10
Board_7-/J2TRG2: J1#4.4, J2#12.4
Board_7-/JB0: J1#4.1, J2#12.1
Board_7-/JB1: J1#4.13, J2#12.13
Board_7-/JB2: J1#4.11, J2#12.11
Board_7-/JB3: J1#4.3, J2#12.3
Board_7-/VCC: J1#4.14, J2#12.14
Board_7-Net-(J1-Pin_5): J1#4.5, J2#12.5
Board_7-Net-(J1-Pin_6): J1#4.6, J2#12.6
Board_7-Net-(J1-Pin_8): J1#4.8, J2#12.8
Board_7-Net-(J1-Pin_9): J1#4.9, J2#12.9
Board_8-/GND: J1#11.7, J2#15.7
Board_8-/J1TRG1: J1#11.2, J2#15.2
Board_8-/J1TRG2: J1#11.10, J2#15.12
Board_8-/J2TRG1: J1#11.12, J2#15.10
Board_8-/J2TRG2: J1#11.4, J2#15.4
Board_8-/JB0: J1#11.1, J2#15.1
Board_8-/JB1: J1#11.13, J2#15.13
Board_8-/JB2: J1#11.11, J2#15.11
Board_8-/JB3: J1#11.3, J2#15.3
Board_8-/VCC: J1#11.14, J2#15.14
Board_8-Net-(J1-Pin_5): J1#11.5, J2#15.5
Board_8-Net-(J1-Pin_6): J1#11.6, J2#15.6
Board_8-Net-(J1-Pin_8): J1#11.8, J2#15.8
Board_8-Net-(J1-Pin_9): J1#11.9, J2#15.9
Board_9-/GND: J1#2.7, J2#14.7
Board_9-/J1TRG1: J1#2.2, J2#14.2
Board_9-/J1TRG2: J1#2.10, J2#14.12
Board_9-/J2TRG1: J1#2.12, J2#14.10
Board_9-/J2TRG2: J1#2.4, J2#14.4
Board_9-/JB0: J1#2.1, J2#14.1
Board_9-/JB1: J1#2.13, J2#14.13
Board_9-/JB2: J1#2.11, J2#14.11
Board_9-/JB3: J1#2.3, J2#14.3
Board_9-/VCC: J1#2.14, J2#14.14
Board_9-Net-(J1-Pin_5): J1#2.5, J2#14.5
Board_9-Net-(J1-Pin_6): J1#2.6, J2#14.6
Board_9-Net-(J1-Pin_8): J1#2.8, J2#14.8
Board_9-Net-(J1-Pin_9): J1#2.9, J2#14.9
Board_10-/GND: J1#16.7, J2#20.7
Board_10-/J1TRG1: J1#16.2, J2#20.2
Board_10-/J1TRG2: J1#16.10, J2#20.12
Board_10-/J2TRG1: J1#16.12, J2#20.10
Board_10-/J2TRG2: J1#16.4, J2#20.4
Board_10-/JB0: J1#16.1, J2#20.1
Board_10-/JB1: J1#16.13, J2#20.13
Board_10-/JB2: J1#16.11, J2#20.11
Board_10-/JB3: J1#16.3, J2#20.3
Board_10-/VCC: J1#16.14, J2#20.14
Board_10-Net-(J1-Pin_5): J1#16.5, J2#20.5
Board_10-Net-(J1-Pin_6): J1#16.6, J2#20.6
Board_10-Net-(J1-Pin_8): J1#16.8, J2#20.8
Board_10-Net-(J1-Pin_9): J1#16.9, J2#20.9
Board_11-/GND: J1#3.7, J2#4.7
Board_11-/J1TRG1: J1#3.2, J2#4.2
Board_11-/J1TRG2: J1#3.10, J2#4.12
Board_11-/J2TRG1: J1#3.12, J2#4.10
Board_11-/J2TRG2: J1#3.4, J2#4.4
Board_11-/JB0: J1#3.1, J2#4.1
Board_11-/JB1: J1#3.13, J2#4.13
Board_11-/JB2: J1#3.11, J2#4.11
Board_11-/JB3: J1#3.3, J2#4.3
Board_11-/VCC: J1#3.14, J2#4.14
Board_11-Net-(J1-Pin_5): J1#3.5, J2#4.5
Board_11-Net-(J1-Pin_6): J1#3.6, J2#4.6
Board_11-Net-(J1-Pin_8): J1#3.8, J2#4.8
Board_11-Net-(J1-Pin_9): J1#3.9, J2#4.9
Board_12-/GND: J1#12.7, J2#11.7
Board_12-/J1TRG1: J1#12.2, J2#11.2
Board_12-/J1TRG2: J1#12.10, J2#11.12
Board_12-/J2TRG1: J1#12.12, J2#11.10
Board_12-/J2TRG2: J1#12.4, J2#11.4
Board_12-/JB0: J1#12.1, J2#11.1
Board_12-/JB1: J1#12.13, J2#11.13
Board_12-/JB2: J1#12.11, J2#11.11
Board_12-/JB3: J1#12.3, J2#11.3
Board_12-/VCC: J1#12.14, J2#11.14
Board_12-Net-(J1-Pin_5): J1#12.5, J2#11.5
Board_12-Net-(J1-Pin_6): J1#12.6, J2#11.6
Board_12-Net-(J1-Pin_8): J1#12.8, J2#11.8
Board_12-Net-(J1-Pin_9): J1#12.9, J2#11.9
Board_13-/GND: J1#7.7, J2#19.7
Board_13-/J1TRG1: J1#7.2, J2#19.2
Board_13-/J1TRG2: J1#7.10, J2#19.12
Board_13-/J2TRG1: J1#7.12, J2#19.10
Board_13-/J2TRG2: J1#7.4, J2#19.4
Board_13-/JB0: J1#7.1, J2#19.1
Board_13-/JB1: J1#7.13, J2#19.13
Board_13-/JB2: J1#7.11, J2#19.11
Board_13-/JB3: J1#7.3, J2#19.3
Board_13-/VCC: J1#7.14, J2#19.14
Board_13-Net-(J1-Pin_5): J1#7.5, J2#19.5
Board_13-Net-(J1-Pin_6): J1#7.6, J2#19.6
Board_13-Net-(J1-Pin_8): J1#7.8, J2#19.8
Board_13-Net-(J1-Pin_9): J1#7.9, J2#19.9
Board_14-/GND: J1#17.7, J2#8.7
Board_14-/J1TRG1: J1#17.2, J2#8.2
Board_14-/J1TRG2: J1#17.10, J2#8.12
Board_14-/J2TRG1: J1#17.12, J2#8.10
Board_14-/J2TRG2: J1#17.4, J2#8.4
Board_14-/JB0: J1#17.1, J2#8.1
Board_14-/JB1: J1#17.13, J2#8.13
Board_14-/JB2: J1#17.11, J2#8.11
Board_14-/JB3: J1#17.3, J2#8.3
Board_14-/VCC: J1#17.14, J2#8.14
Board_14-Net-(J1-Pin_5): J1#17.5, J2#8.5
Board_14-Net-(J1-Pin_6): J1#17.6, J2#8.6
Board_14-Net-(J1-Pin_8): J1#17.8, J2#8.8
Board_14-Net-(J1-Pin_9): J1#17.9, J2#8.9
Board_15-/GND: J1#20.7, J2#9.7
Board_15-/J1TRG1: J1#20.2, J2#9.2
Board_15-/J1TRG2: J1#20.10, J2#9.12
Board_15-/J2TRG1: J1#20.12, J2#9.10
Board_15-/J2TRG2: J1#20.4, J2#9.4
Board_15-/JB0: J1#20.1, J2#9.1
Board_15-/JB1: J1#20.13, J2#9.13
Board_15-/JB2: J1#20.11, J2#9.11
Board_15-/JB3: J1#20.3, J2#9.3
Board_15-/VCC: J1#20.14, J2#9.14
Board_15-Net-(J1-Pin_5): J1#20.5, J2#9.5
Board_15-Net-(J1-Pin_6): J1#20.6, J2#9.6
Board_15-Net-(J1-Pin_8): J1#20.8, J2#9.8
Board_15-Net-(J1-Pin_9): J1#20.9, J2#9.9
Board_16-/GND: J1#10.7, J2.7
Board_16-/J1TRG1: J1#10.2, J2.2
Board_16-/J1TRG2: J1#10.10, J2.12
Board_16-/J2TRG1: J1#10.12, J2.10
Board_16-/J2TRG2: J1#10.4, J2.4
Board_16-/JB0: J1#10.1, J2.1
Board_16-/JB1: J1#10.13, J2.13
Board_16-/JB2: J1#10.11, J2.11
Board_16-/JB3: J1#10.3, J2.3
Board_16-/VCC: J1#10.14, J2.14
Board_16-Net-(J1-Pin_5): J1#10.5, J2.5
Board_16-Net-(J1-Pin_6): J1#10.6, J2.6
Board_16-Net-(J1-Pin_8): J1#10.8, J2.8
Board_16-Net-(J1-Pin_9): J1#10.9, J2.9
Board_17-/GND: J1#5.7, J2#5.7
Board_17-/J1TRG1: J1#5.2, J2#5.2
Board_17-/J1TRG2: J1#5.10, J2#5.12
Board_17-/J2TRG1: J1#5.12, J2#5.10
Board_17-/J2TRG2: J1#5.4, J2#5.4
Board_17-/JB0: J1#5.1, J2#5.1
Board_17-/JB1: J1#5.13, J2#5.13
Board_17-/JB2: J1#5.11, J2#5.11
Board_17-/JB3: J1#5.3, J2#5.3
Board_17-/VCC: J1#5.14, J2#5.14
Board_17-Net-(J1-Pin_5): J1#5.5, J2#5.5
Board_17-Net-(J1-Pin_6): J1#5.6, J2#5.6
Board_17-Net-(J1-Pin_8): J1#5.8, J2#5.8
Board_17-Net-(J1-Pin_9): J1#5.9, J2#5.9
Board_18-/GND: J1#13.7, J2#3.7
Board_18-/J1TRG1: J1#13.2, J2#3.2
Board_18-/J1TRG2: J1#13.10, J2#3.12
Board_18-/J2TRG1: J1#13.12, J2#3.10
Board_18-/J2TRG2: J1#13.4, J2#3.4
Board_18-/JB0: J1#13.1, J2#3.1
Board_18-/JB1: J1#13.13, J2#3.13
Board_18-/JB2: J1#13.11, J2#3.11
Board_18-/JB3: J1#13.3, J2#3.3
Board_18-/VCC: J1#13.14, J2#3.14
Board_18-Net-(J1-Pin_5): J1#13.5, J2#3.5
Board_18-Net-(J1-Pin_6): J1#13.6, J2#3.6
Board_18-Net-(J1-Pin_8): J1#13.8, J2#3.8
Board_18-Net-(J1-Pin_9): J1#13.9, J2#3.9
Board_19-/GND: J1#18.7, J2#16.7
Board_19-/J1TRG1: J1#18.2, J2#16.2
Board_19-/J1TRG2: J1#18.10, J2#16.12
Board_19-/J2TRG1: J1#18.12, J2#16.10
Board_19-/J2TRG2: J1#18.4, J2#16.4
Board_19-/JB0: J1#18.1, J2#16.1
Board_19-/JB1: J1#18.13, J2#16.13
Board_19-/JB2: J1#18.11, J2#16.11
Board_19-/JB3: J1#18.3, J2#16.3
Board_19-/VCC: J1#18.14, J2#16.14
Board_19-Net-(J1-Pin_5): J1#18.5, J2#16.5
Board_19-Net-(J1-Pin_6): J1#18.6, J2#16.6
Board_19-Net-(J1-Pin_8): J1#18.8, J2#16.8
Board_19-Net-(J1-Pin_9): J1#18.9, J2#16.9

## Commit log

2025-10-04 Initial commit.
2025-10-04 Add LICENSE
2025-10-04 readme: remove spurious dot, add Ludo's board picture
2025-10-04 readme: now yes, add Ludo's board picture
2025-10-04 readme: fix bad link, add notes, enhance redaction
2026-02-27 fix htmlpreview link
